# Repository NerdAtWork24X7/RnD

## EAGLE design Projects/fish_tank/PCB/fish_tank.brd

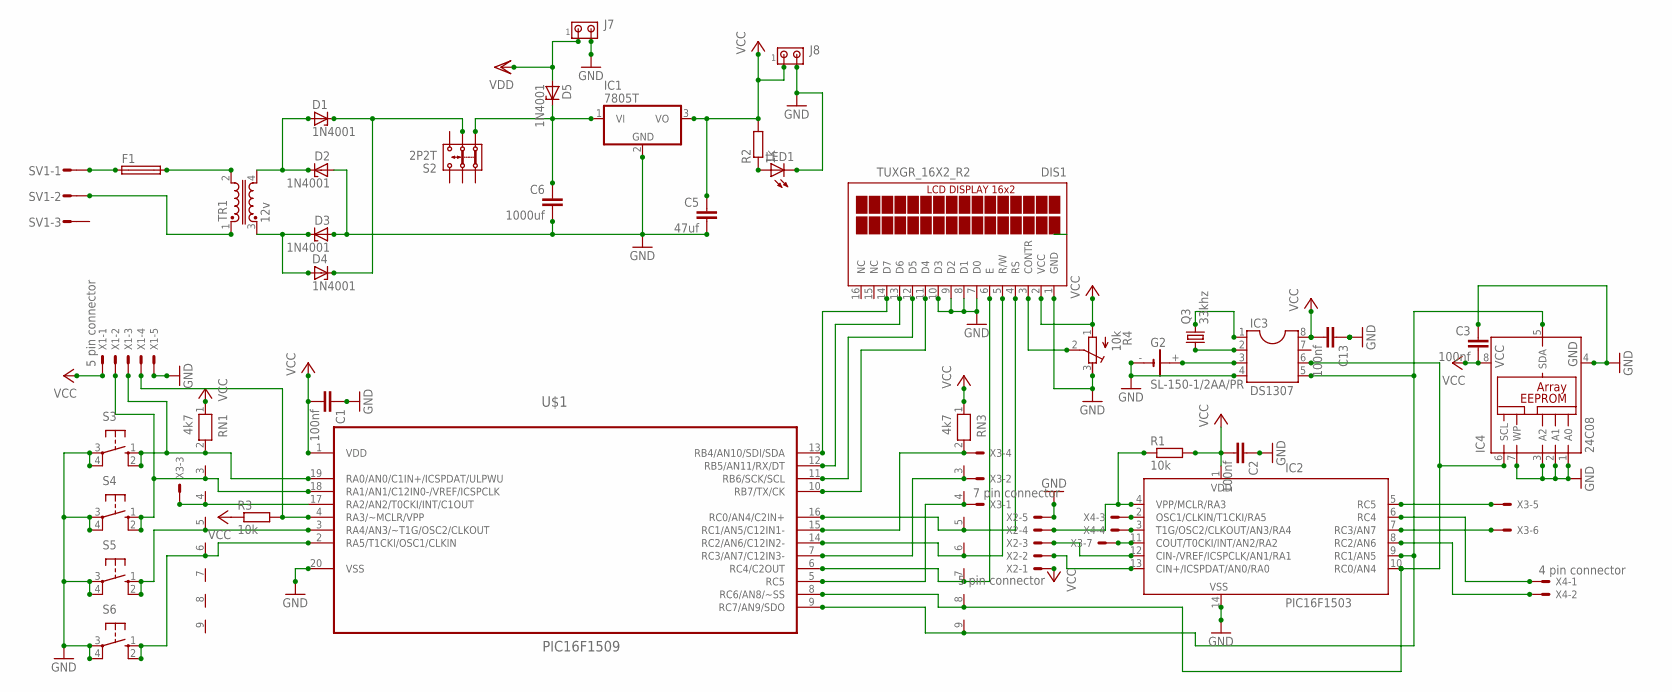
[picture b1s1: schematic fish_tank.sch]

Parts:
C1, C2: 100nf; C2.5-4
C3, C13: 100nf; C5B2.5
C5: 47uf; C5B2.5
C6: 1000uf; C5B2.5
D1, D2, D3, D4, D5: 1N4001; DO35Z10
DIS1: TUXGR_16X2_R2
F1: SH25
G2: SL-150-1/2AA/PR
IC1: 7805T; TO220H
IC2: PIC16F1503; DIL14
IC3: DS1307; DIL08
IC4: 24C08; DIL8
J7, J8: MTA02-100; 10X02MTA
LED1: LED3MM
Q3: 33khz; TC26H
R1, R3: 10k; 0207/7
R2: 1k; 0204/5
R4: 10k; RTRIM64W
RN1, RN3: 4k7; RN-9
S2: 2P2T
S3, S4, S5, S6: 10-XX; B3F-10XX
SV1: MT6-3Y
TR1: 12v; U15
U$1: PIC16F1509; DIP254P762X533-20
X1, X2: 5 pin connector; 22-23-2051
X3: 7 pin connector; 22-23-2071
X4: 4 pin connector; 22-23-2041

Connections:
GND: C1.1, C2.1, C3.1, C5.2, C6.2, C13.1, D2.A, D3.A, DIS1.1 (GND), DIS1.7 (D0), DIS1.8 (D1), DIS1.9 (D2), DIS1.10 (D3), G2.-, IC1.2 (GND), IC2.14 (VSS), IC3.4, IC4.1 (A0), IC4.2 (A1), IC4.3 (A2), IC4.4 (GND), IC4.7 (WP), J7.2, J8.2, LED1.K (C), R4.3 (E), S3.3, S3.4 (P1), S4.3, S4.4 (P1), S5.3, S5.4 (P1), S6.3, S6.4 (P1), U$1.20 (VSS), X1.5, X2.5
unnamed: D3.C, D4.A, TR1.3
unnamed: D1.A, D2.C, TR1.4
unnamed: RN1.5, S5.1 (S), S5.2 (S1), U$1.3 (RA4/AN3/~T1G/OSC2/CLKOUT)
unnamed: DIS1.3 (CONTR), R4.2 (S)
unnamed: RN1.6, S6.1 (S), S6.2 (S1), U$1.2 (RA5/T1CKI/OSC1/CLKIN)
unnamed: C6.1, D5.C, IC1.1 (VI), S2.1.2
unnamed: RN1.2, S3.1 (S), S3.2 (S1), U$1.19 (RA0/AN0/C1IN+/ICSPDAT/ULPWU), X1.3
unnamed: RN1.3, S4.1 (S), S4.2 (S1), U$1.18 (RA1/AN1/C12IN0-/VREF/ICSPCLK), X1.2
unnamed: IC2.13 (CIN+/ICSPDAT/AN0/RA0), X2.2
unnamed: IC2.6 (RC4), X4.1
unnamed: IC2.4 (VPP/MCLR/RA3), R1.1, X2.4
unnamed: DIS1.6 (E), RN3.7, U$1.6 (RC4/C2OUT)
unnamed: IC2.5 (RC5), X3.5
unnamed: IC2.7 (RC3/AN7), X3.6
unnamed: DIS1.4 (RS), RN3.5, U$1.16 (RC0/AN4/C2IN+)
unnamed: DIS1.5 (R/W), RN3.6, U$1.14 (RC2/AN6/C12IN2-)
unnamed: IC2.10 (RC0/AN4), IC3.6, IC4.6 (SCL), RN3.8, U$1.8 (RC6/AN8/~SS)
unnamed: IC2.11 (COUT/T0CKI/INT/AN2/RA2), X3.7
unnamed: IC2.12 (CIN-/VREF/ICSPCLK/AN1/RA1), X2.3
unnamed: IC2.9 (RC1/AN5), IC3.5, IC4.5 (SDA), RN3.9, U$1.9 (RC7/AN9/SDO)
unnamed: RN1.4, U$1.17 (RA2/AN2/T0CKI/INT/C1OUT), X3.3
unnamed: RN3.2, U$1.15 (RC1/AN5/C12IN1-), X3.4
unnamed: RN3.3, U$1.7 (RC3/AN7/C12IN3-), X3.2
unnamed: RN3.4, U$1.5 (RC5), X3.1
unnamed: DIS1.14 (D7), U$1.13 (RB4/AN10/SDI/SDA)
unnamed: DIS1.13 (D6), U$1.12 (RB5/AN11/RX/DT)
unnamed: DIS1.12 (D5), U$1.11 (RB6/SCK/SCL)
unnamed: DIS1.11 (D4), U$1.10 (RB7/TX/CK)
unnamed: R3.2, U$1.4 (RA3/~MCLR/VPP), X1.4
unnamed: IC2.8 (RC2/AN6), X4.2
unnamed: IC2.2 (OSC1/CLKIN/T1CKI/RA5), X4.3
unnamed: IC2.3 (T1G/OSC2/CLKOUT/AN3/RA4), X4.4
unnamed: SV1.2, TR1.1
unnamed: F1.1, SV1.1
unnamed: F1.2, TR1.2
unnamed: G2.+, IC3.3
unnamed: IC3.2, Q3.1
unnamed: D1.C, D4.C, S2.2.2
unnamed: LED1.A, R2.1
unnamed: IC3.1, Q3.2
VCC: C1.2, C2.2, C3.2, C5.1, C13.2, DIS1.2 (VCC), IC1.3 (VO), IC2.1 (VDD), IC3.8, IC4.8 (VCC), J8.1, R1.2, R2.2, R3.1, R4.1 (A), RN1.1, RN3.1, U$1.1 (VDD), X1.1, X2.1
VDD: D5.A, J7.1

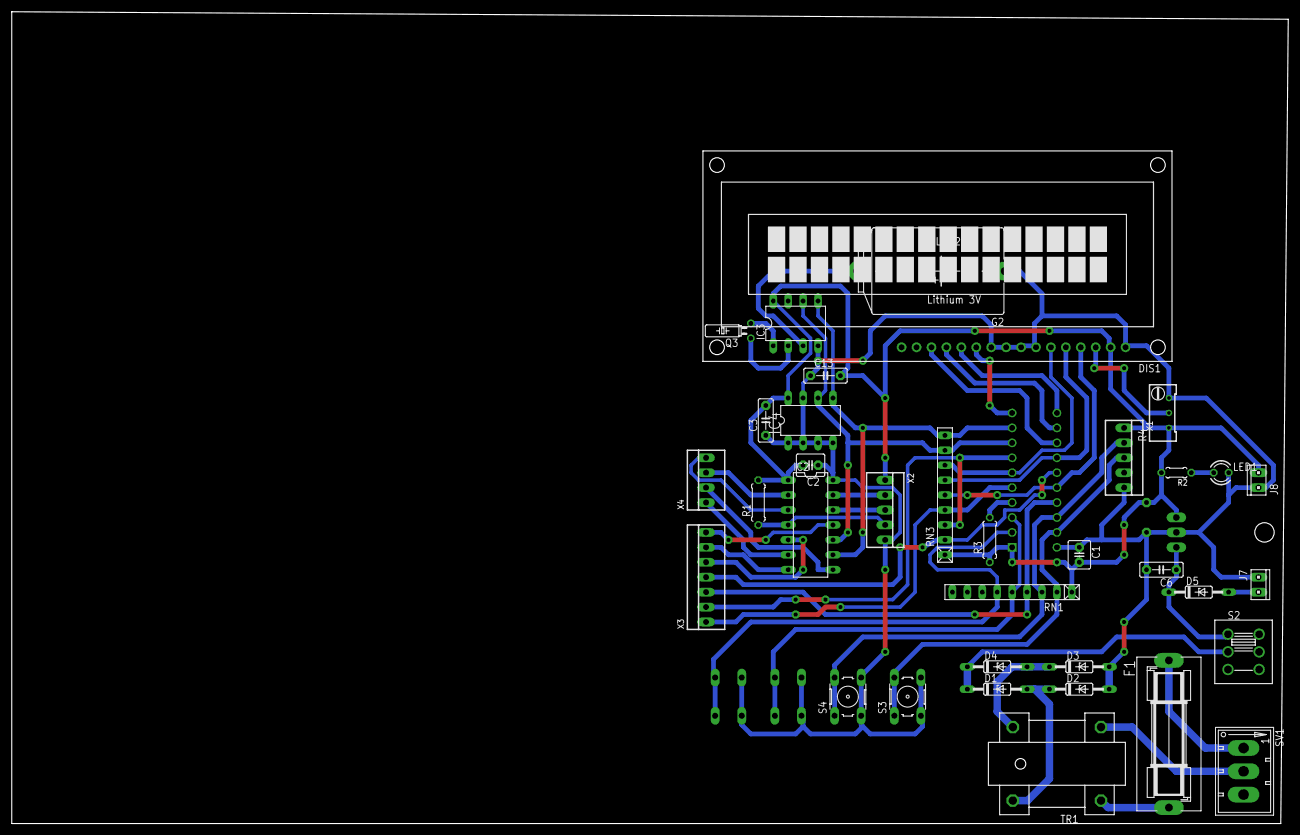
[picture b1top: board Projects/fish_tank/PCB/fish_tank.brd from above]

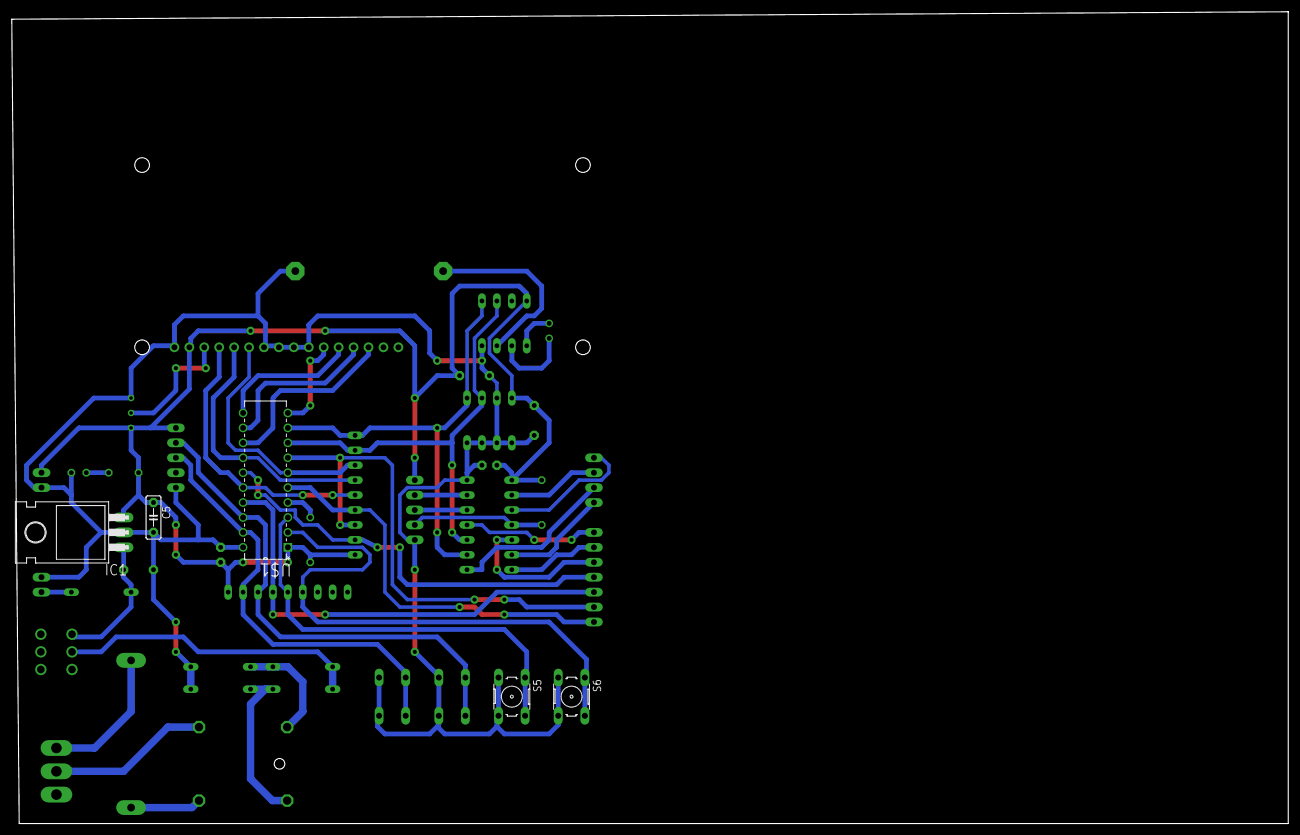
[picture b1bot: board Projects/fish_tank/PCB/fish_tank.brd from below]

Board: 2 copper layers, 217.2 x 138.1 mm, 40 parts (5 on the bottom side), 43 nets.

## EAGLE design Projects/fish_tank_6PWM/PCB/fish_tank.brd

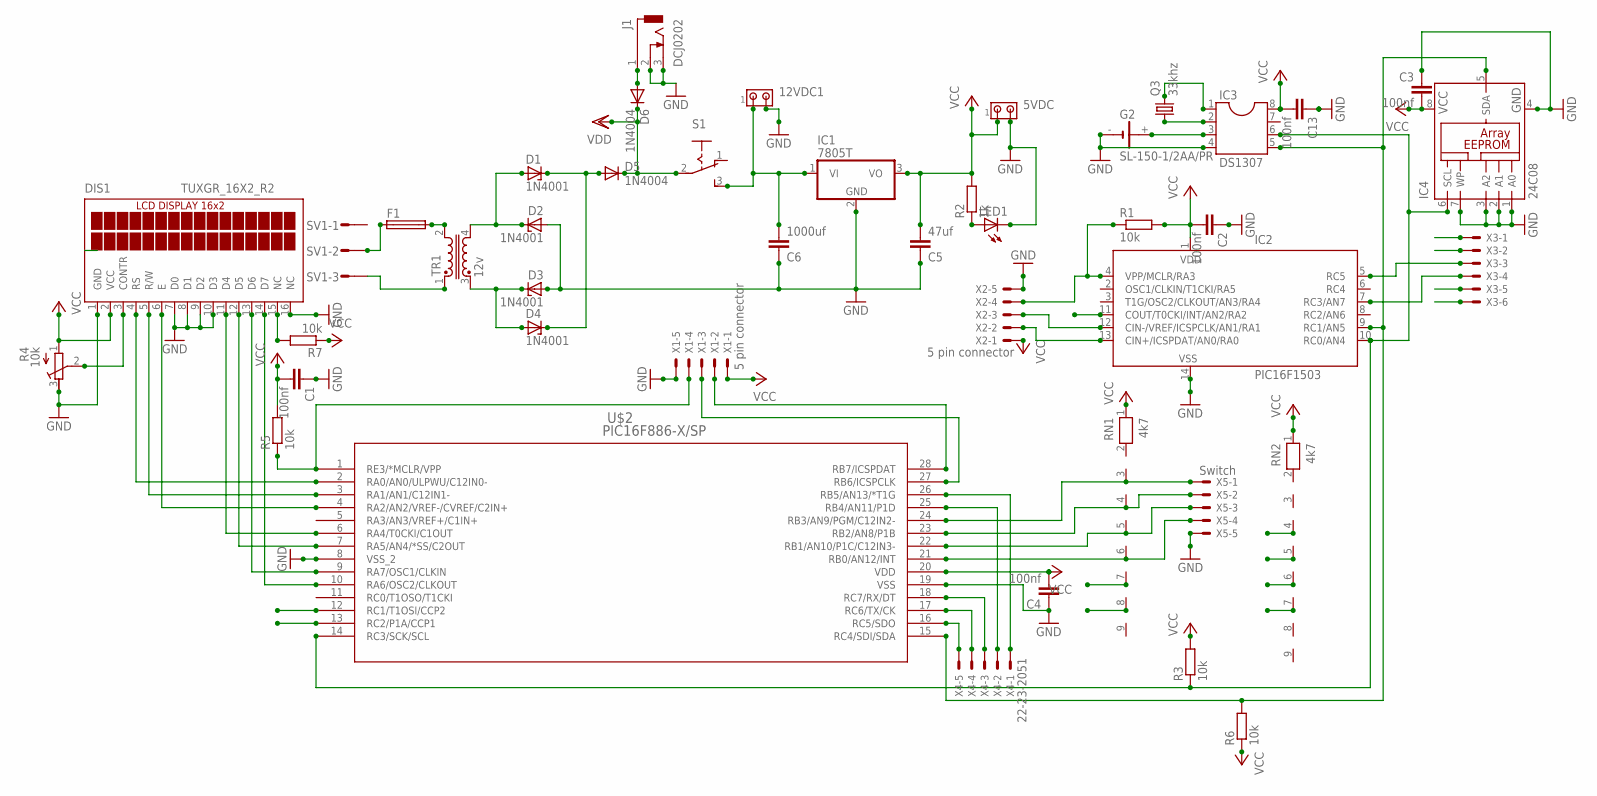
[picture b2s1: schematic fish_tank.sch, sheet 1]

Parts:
5VDC, 12VDC1: MTA02-100; 10X02MTA
C1, C2, C4: 100nf; C2.5-4
C3, C13: 100nf; C5B2.5
C5: 47uf; C5B2.5
C6: 1000uf; C5B2.5
D1, D2, D3, D4: 1N4001; DO35Z10
D5, D6: 1N4004; DO41-10
DIS1: TUXGR_16X2_R2
F1: SH25
G2: SL-150-1/2AA/PR
IC1: 7805T; TO220H
IC2: PIC16F1503; DIL14
IC3: DS1307; DIL08
IC4: 24C08; DIL8
J1: DCJ0202
LED1: LED3MM
Q3: 33khz; TC26H
R1, R3, R5, R6, R7: 10k; 0207/7
R2: 1k; 0204/5
R4: 10k; RTRIM64W
RN1, RN2: 4k7; RN-9
S1: 255SB
SV1: MT6-3Y
TR1: 12v; U15
U$2: PIC16F886-X/SP; SPDIP28_300MC
X1, X2: 5 pin connector; 22-23-2051
X3: 22-23-2061
X4: 22-23-2051
X5: Switch; 22-23-2051

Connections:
GND: 5VDC.2, 12VDC1.2, C1.1, C2.1, C3.1, C4.1, C5.1, C6.1, C13.1, D2.A, D3.A, DIS1.1 (GND), DIS1.7 (D0), DIS1.8 (D1), DIS1.9 (D2), DIS1.10 (D3), DIS1.16 (NC), G2.-, IC1.2 (GND), IC2.14 (VSS), IC3.4, IC4.1 (A0), IC4.2 (A1), IC4.3 (A2), IC4.4 (GND), IC4.7 (WP), J1.2, J1.3, LED1.K (C), R4.3 (E), U$2.8 (VSS_2), U$2.19 (VSS), X1.5, X2.5, X5.5
unnamed: D3.C, D4.A, TR1.3
unnamed: D1.A, D2.C, TR1.4
unnamed: RN1.5, U$2.22 (RB1/AN10/P1C/C12IN3-), X5.3
unnamed: DIS1.3 (CONTR), R4.2 (S)
unnamed: RN1.6, U$2.21 (RB0/AN12/INT), X5.4
unnamed: IC2.10 (RC0/AN4), IC3.6, IC4.6 (SCL), R3.1, U$2.14 (RC3/SCK/SCL)
unnamed: RN1.3, U$2.24 (RB3/AN9/PGM/C12IN2-), X5.1
unnamed: DIS1.4 (RS), U$2.2 (RA0/AN0/ULPWU/C12IN0-)
unnamed: IC2.13 (CIN+/ICSPDAT/AN0/RA0), X2.2
unnamed: DIS1.5 (R/W), U$2.3 (RA1/AN1/C12IN1-)
unnamed: IC2.4 (VPP/MCLR/RA3), R1.1, X2.4
unnamed: DIS1.6 (E), U$2.4 (RA2/AN2/VREF-/CVREF/C2IN+)
unnamed: IC2.9 (RC1/AN5), IC3.5, IC4.5 (SDA), R6.2, U$2.15 (RC4/SDI/SDA)
unnamed: U$2.26 (RB5/AN13/*T1G), X4.1
unnamed: F1.1, SV1.2
unnamed: U$2.25 (RB4/AN11/P1D), X4.2
unnamed: U$2.16 (RC5/SDO), X4.5
unnamed: U$2.17 (RC6/TX/CK), X4.4
unnamed: IC2.12 (CIN-/VREF/ICSPCLK/AN1/RA1), X2.3
unnamed: U$2.18 (RC7/RX/DT), X4.3
unnamed: RN1.4, U$2.23 (RB2/AN8/P1B), X5.2
unnamed: D6.A, J1.1
unnamed: 12VDC1.1, C6.2, IC1.1 (VI), S1.3 (S)
unnamed: IC2.7 (RC3/AN7), X3.4
unnamed: DIS1.14 (D7), U$2.10 (RA6/OSC2/CLKOUT)
unnamed: DIS1.13 (D6), U$2.9 (RA7/OSC1/CLKIN)
unnamed: DIS1.12 (D5), U$2.7 (RA5/AN4/*SS/C2OUT)
unnamed: DIS1.11 (D4), U$2.6 (RA4/T0CKI/C1OUT)
unnamed: U$2.27 (RB6/ICSPCLK), X1.3
unnamed: DIS1.15 (NC), R7.2
unnamed: U$2.28 (RB7/ICSPDAT), X1.2
unnamed: R5.1, U$2.1 (RE3/*MCLR/VPP), X1.4
unnamed: SV1.3, TR1.1
unnamed: F1.2, TR1.2
unnamed: G2.+, IC3.3
unnamed: IC3.2, Q3.1
unnamed: D1.C, D4.C, D5.A
unnamed: LED1.A, R2.1
unnamed: IC3.1, Q3.2
PWM1: RN1.7, U$2.13 (RC2/P1A/CCP1), X3.1
PWM2: RN1.8, U$2.12 (RC1/T1OSI/CCP2), X3.2
PWM3: IC2.5 (RC5), RN2.4, X3.3
PWM4: RN2.5
PWM5: IC2.11 (COUT/T0CKI/INT/AN2/RA2), RN2.6, X3.5
PWM6: RN2.7, X3.6
VCC: 5VDC.1, C1.2, C2.2, C3.2, C4.2, C5.2, C13.2, DIS1.2 (VCC), IC1.3 (VO), IC2.1 (VDD), IC3.8, IC4.8 (VCC), R1.2, R2.2, R3.2, R4.1 (A), R5.2, R6.1, R7.1, RN1.1, RN2.1, U$2.20 (VDD), X1.1, X2.1
VDD: D5.C, D6.C, S1.2

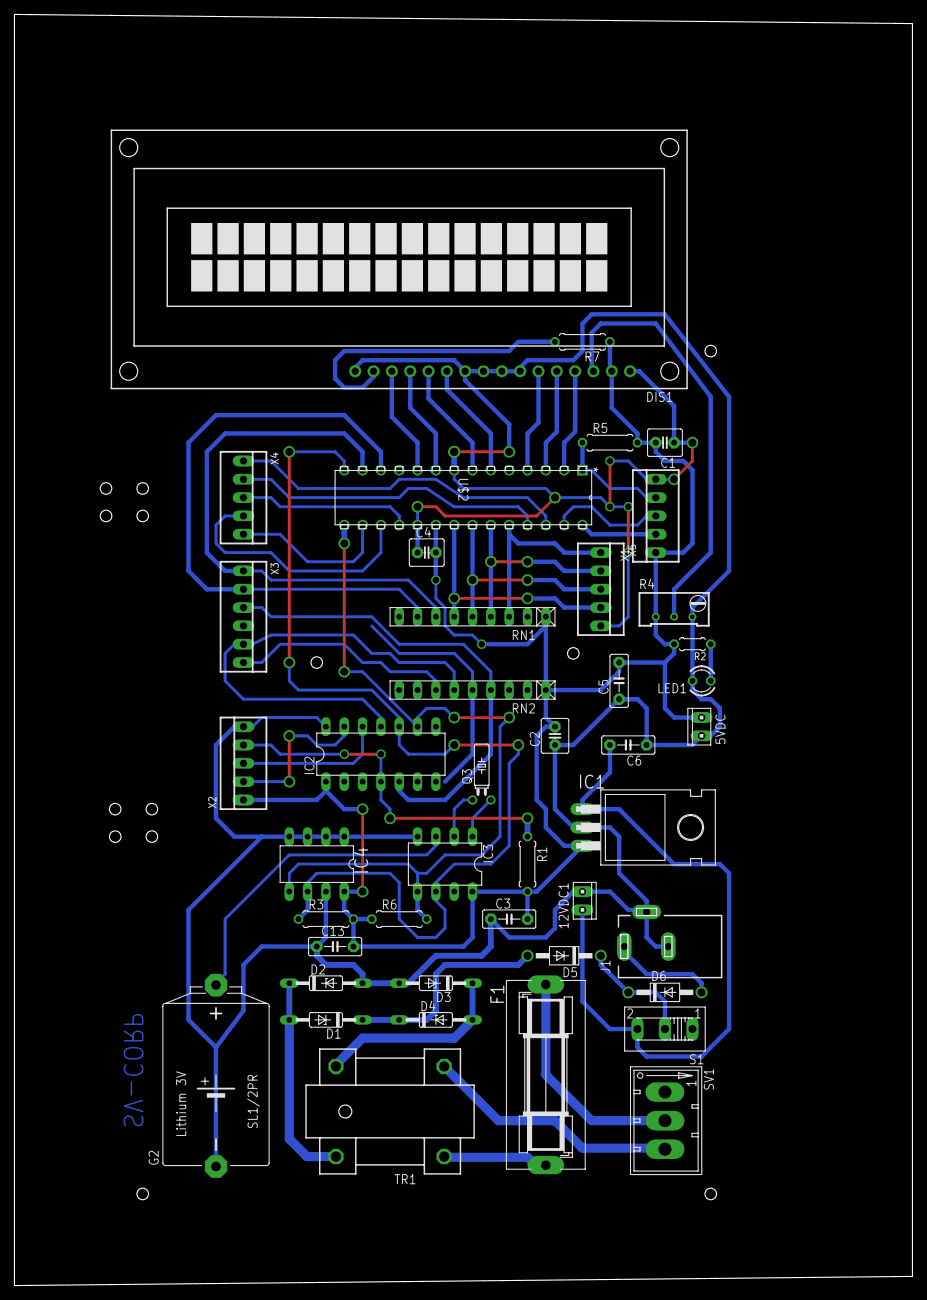
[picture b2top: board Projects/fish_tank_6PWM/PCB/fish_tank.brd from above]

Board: 2 copper layers, 124.5 x 176.2 mm, 43 parts (0 on the bottom side), 47 nets.

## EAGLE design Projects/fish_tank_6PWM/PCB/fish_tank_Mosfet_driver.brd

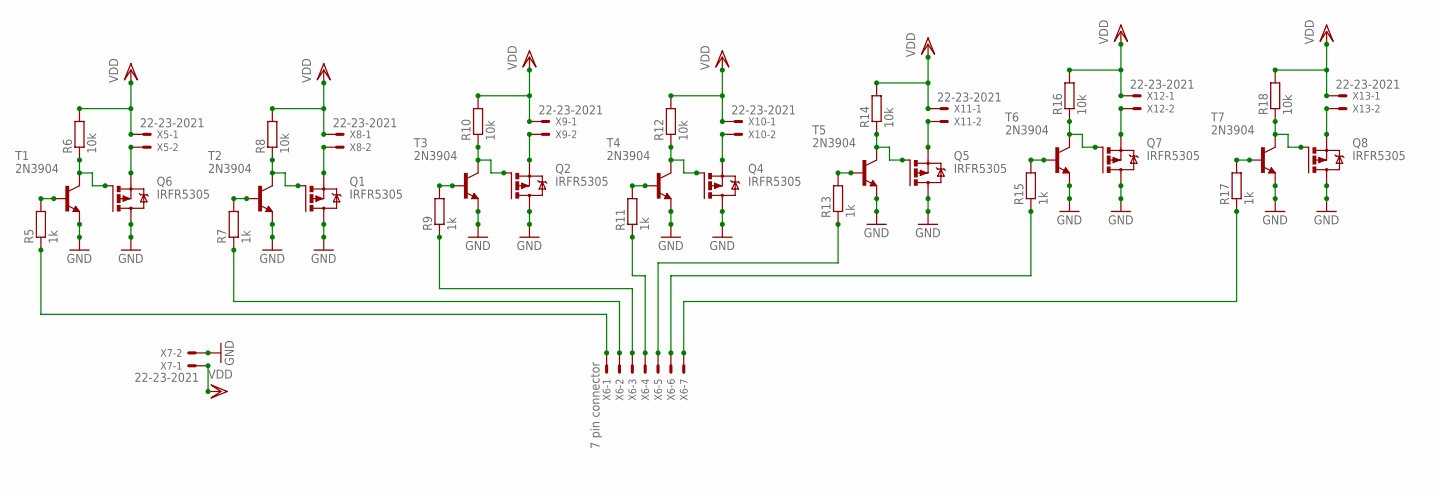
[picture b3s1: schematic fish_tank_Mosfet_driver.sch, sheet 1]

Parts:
Q1, Q2, Q4, Q5, Q6, Q7, Q8: IRFR5305; D-PAK_TO252AA
R5, R7, R9, R11, R13, R15, R17: 1k; 0207/7
R6, R8, R10, R12, R14, R16, R18: 10k; 0207/7
T1, T2, T3, T4, T5, T6, T7: 2N3904; TO92
X5, X7, X8, X9, X10, X11, X12, X13: 22-23-2021
X6: 7 pin connector; 22-23-2071

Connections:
GND: Q1.4 (D), Q2.4 (D), Q4.4 (D), Q5.4 (D), Q6.4 (D), Q7.4 (D), Q8.4 (D), T1.3 (E), T2.3 (E), T3.3 (E), T4.3 (E), T5.3 (E), T6.3 (E), T7.3 (E), X7.2
unnamed: Q6.1 (G), R6.1, T1.1 (C)
unnamed: R5.2, T1.2 (B)
unnamed: Q6.3 (S), X5.2
unnamed: R5.1, X6.1
unnamed: Q1.1 (G), R8.1, T2.1 (C)
unnamed: R7.2, T2.2 (B)
unnamed: Q1.3 (S), X8.2
unnamed: R7.1, X6.2
unnamed: Q2.1 (G), R10.1, T3.1 (C)
unnamed: R9.2, T3.2 (B)
unnamed: Q2.3 (S), X9.2
unnamed: R9.1, X6.3
unnamed: Q4.1 (G), R12.1, T4.1 (C)
unnamed: R11.2, T4.2 (B)
unnamed: Q4.3 (S), X10.2
unnamed: R11.1, X6.4
unnamed: Q5.1 (G), R14.1, T5.1 (C)
unnamed: R13.2, T5.2 (B)
unnamed: Q5.3 (S), X11.2
unnamed: R13.1, X6.5
unnamed: Q7.1 (G), R16.1, T6.1 (C)
unnamed: R15.2, T6.2 (B)
unnamed: Q7.3 (S), X12.2
unnamed: R15.1, X6.6
unnamed: Q8.1 (G), R18.1, T7.1 (C)
unnamed: R17.2, T7.2 (B)
unnamed: Q8.3 (S), X13.2
unnamed: R17.1, X6.7
VDD: R6.2, R8.2, R10.2, R12.2, R14.2, R16.2, R18.2, X5.1, X7.1, X8.1, X9.1, X10.1, X11.1, X12.1, X13.1

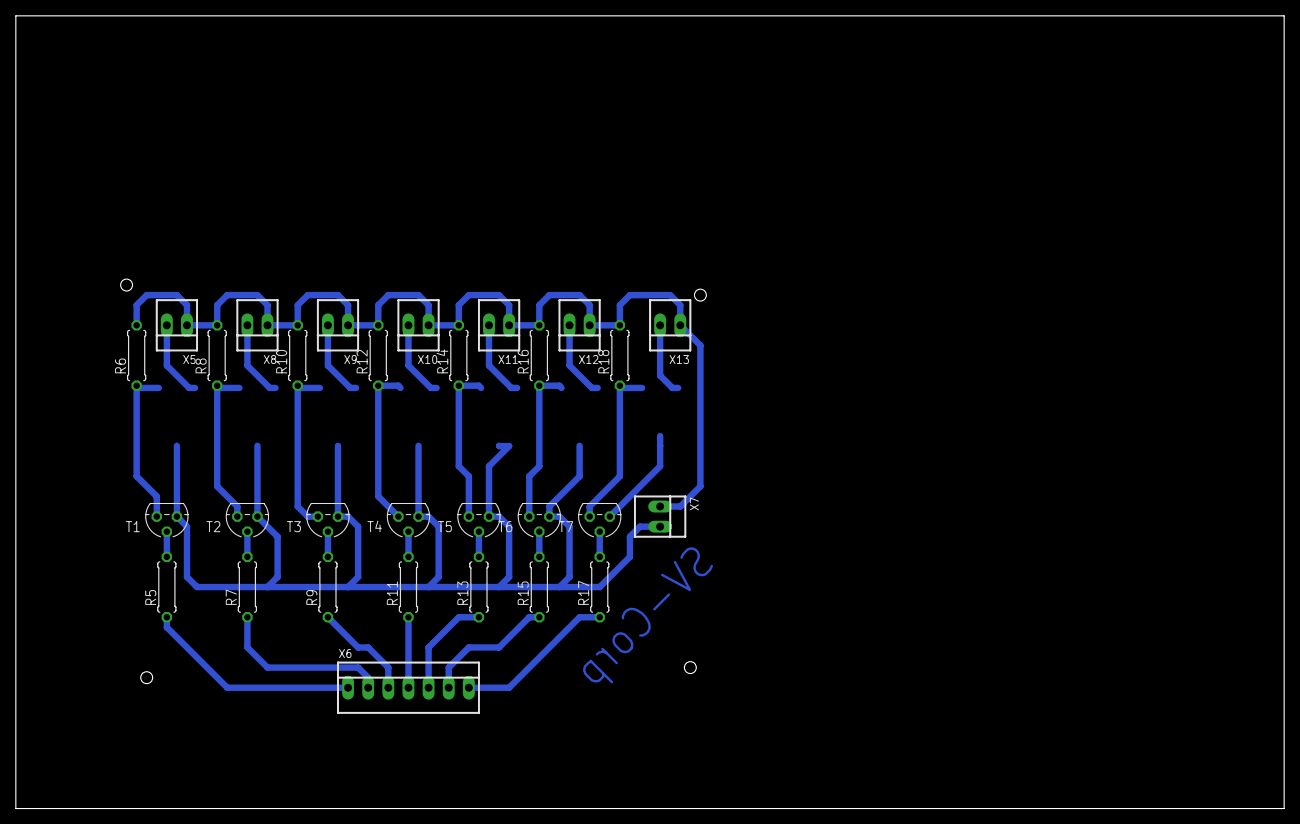
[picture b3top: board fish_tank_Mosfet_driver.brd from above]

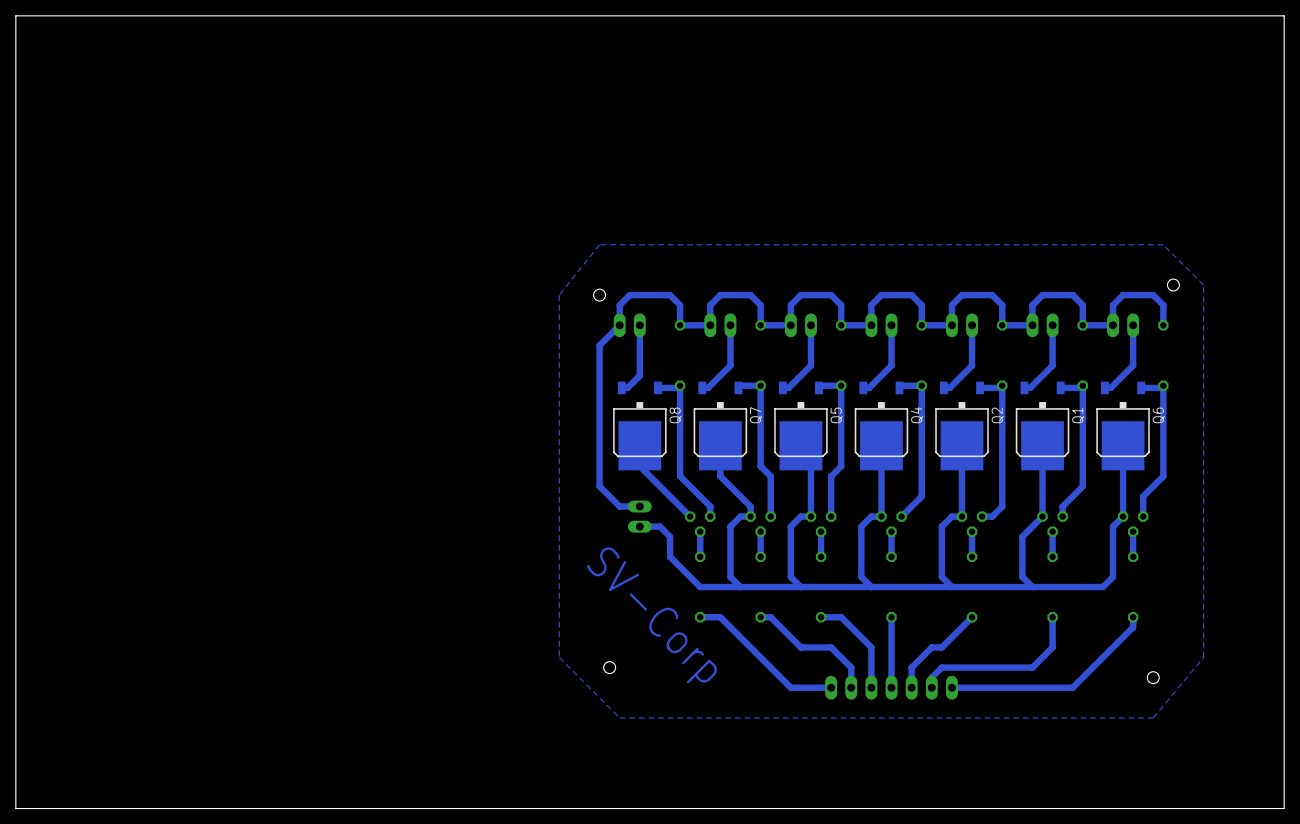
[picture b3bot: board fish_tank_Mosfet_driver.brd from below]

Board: 2 copper layers, 160.0 x 100.0 mm, 37 parts (7 on the bottom side), 30 nets.

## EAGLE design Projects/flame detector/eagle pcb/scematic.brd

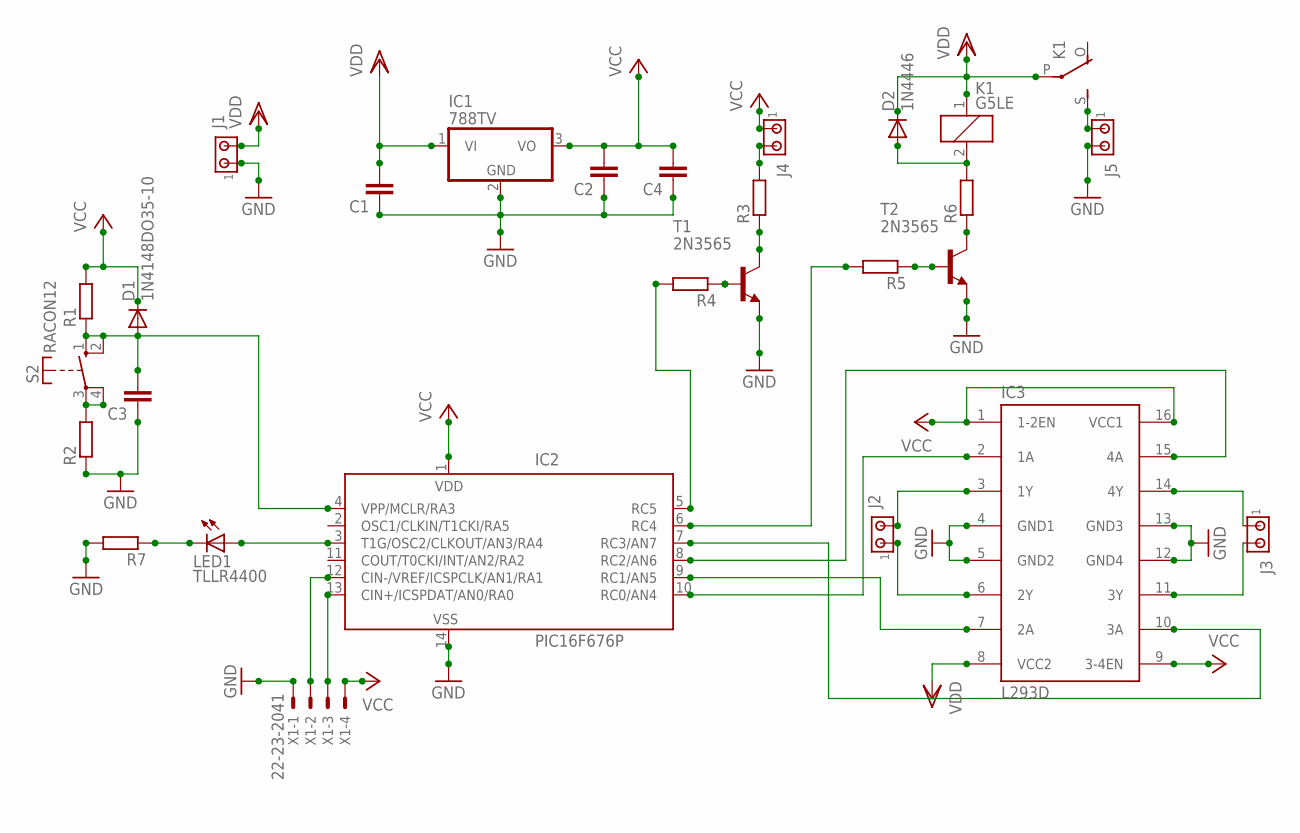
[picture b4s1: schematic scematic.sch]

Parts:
C1, C2, C3, C4: C7.5/3; C7.5B3
D1: 1N4148DO35-10; DO35-10
D2: 1N4446; DO35-10
IC1: 788TV; TO220V
IC2: PIC16F676P; DIL14
IC3: L293D; DIL16
J1, J2, J3, J4, J5: MTA02-156; 1X2MTA
K1: G5LE
LED1: TLLR4400; LED3MM
R1, R2, R3, R4, R5, R6, R7: R-EU_0207/10; 0207/10
S2: RACON12
T1, T2: 2N3565; TO92
X1: 22-23-2041

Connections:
GND: C1.1, C2.1, C3.1, C4.1, IC1.2 (GND), IC2.14 (VSS), IC3.4 (GND1), IC3.5 (GND2), IC3.12 (GND4), IC3.13 (GND3), J1.1, J5.2, R2.1, R7.2, T1.3 (E), T2.3 (E), X1.1
unnamed: C3.2, D1.A, IC2.4 (VPP/MCLR/RA3), R1.1, S2.1 (S), S2.2 (S)
unnamed: IC2.10 (RC0/AN4), IC3.2 (1A)
unnamed: IC2.9 (RC1/AN5), IC3.7 (2A)
unnamed: R2.2, S2.3, S2.4
unnamed: IC3.3 (1Y), J2.2
unnamed: IC3.6 (2Y), J2.1
unnamed: IC3.14 (4Y), J3.1
unnamed: IC3.11 (3Y), J3.2
unnamed: IC2.8 (RC2/AN6), IC3.15 (4A)
unnamed: IC2.7 (RC3/AN7), IC3.10 (3A)
unnamed: IC2.5 (RC5), R4.2
unnamed: R4.1, T1.2 (B)
unnamed: R3.1, T1.1 (C)
unnamed: J4.2, R3.2
unnamed: IC2.6 (RC4), R5.2
unnamed: R5.1, T2.2 (B)
unnamed: R6.1, T2.1 (C)
unnamed: D2.A, K1.2, R6.2
unnamed: J5.1, K1.S
unnamed: IC2.13 (CIN+/ICSPDAT/AN0/RA0), X1.3
unnamed: IC2.12 (CIN-/VREF/ICSPCLK/AN1/RA1), X1.2
unnamed: IC2.3 (T1G/OSC2/CLKOUT/AN3/RA4), LED1.A
unnamed: LED1.K (C), R7.1
VCC: C2.2, C4.2, D1.C, IC1.3 (VO), IC2.1 (VDD), IC3.1 (1-2EN), IC3.9 (3-4EN), IC3.16 (VCC1), J4.1, R1.2, X1.4
VDD: C1.2, D2.C, IC1.1 (VI), IC3.8 (VCC2), J1.2, K1.1, K1.P

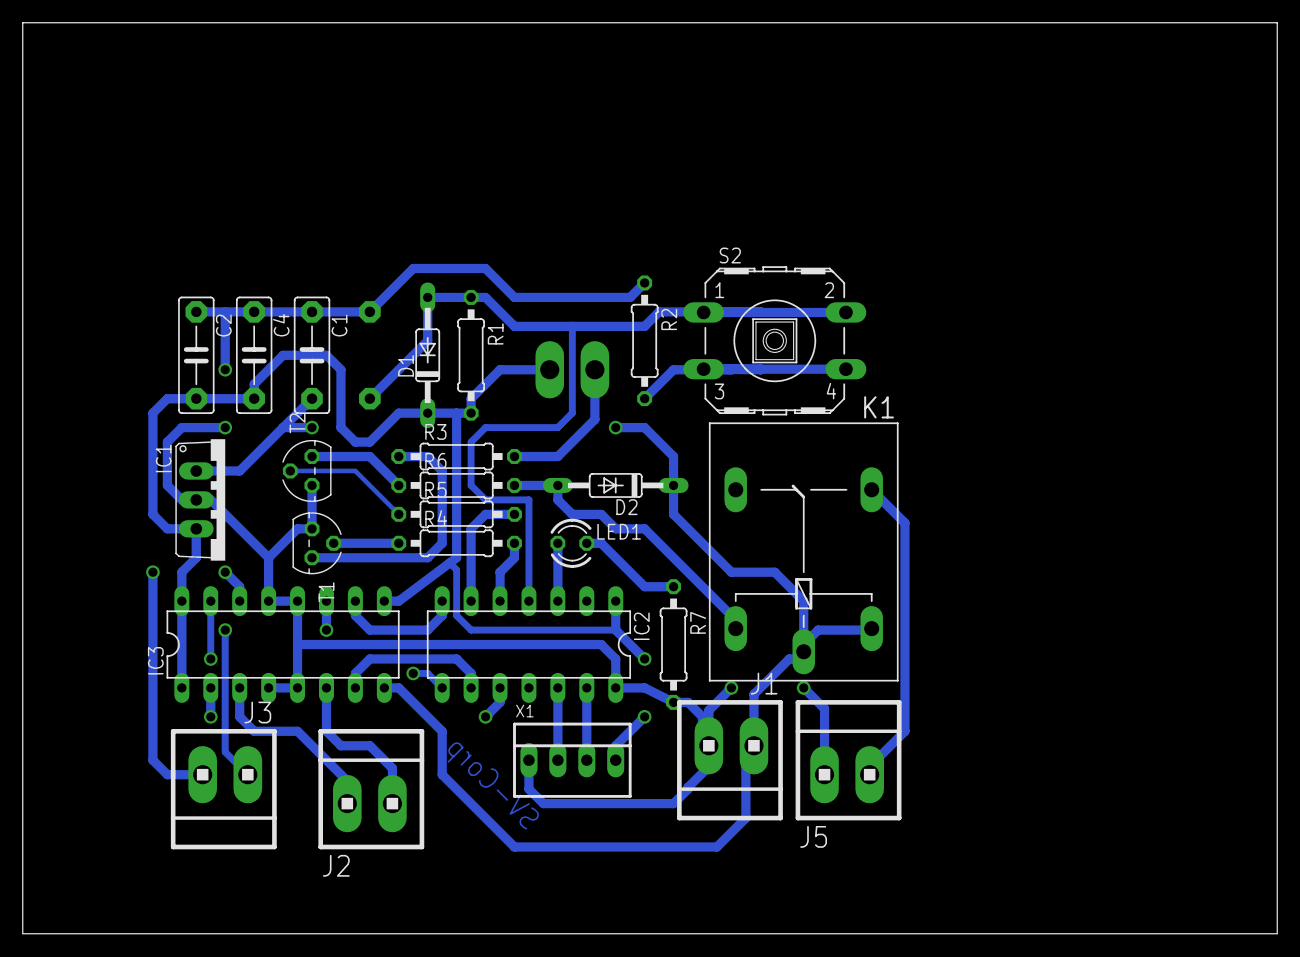
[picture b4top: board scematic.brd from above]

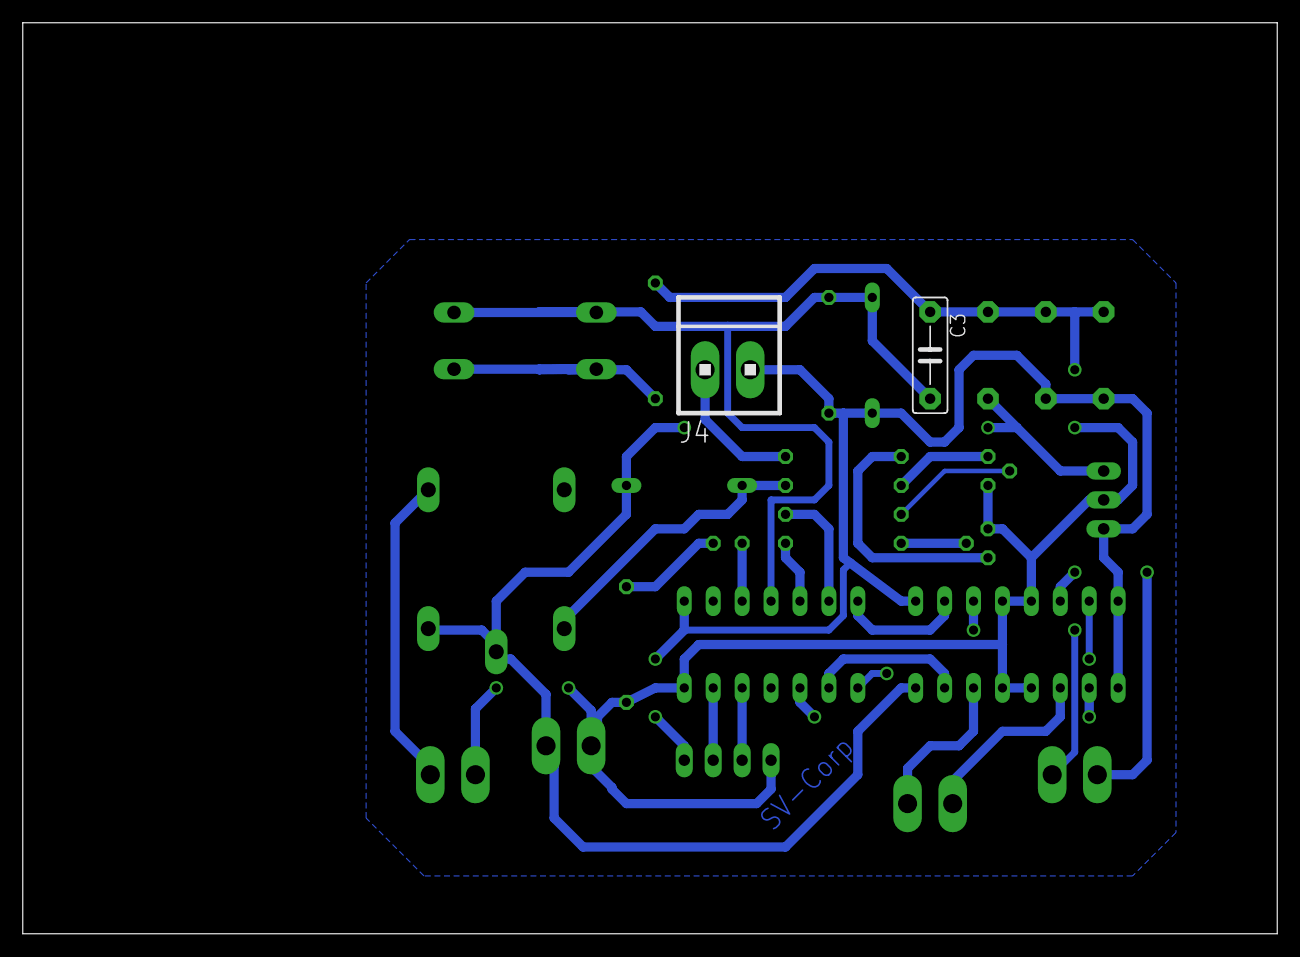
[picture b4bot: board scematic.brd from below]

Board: 2 copper layers, 110.2 x 80.0 mm, 27 parts (2 on the bottom side), 26 nets.

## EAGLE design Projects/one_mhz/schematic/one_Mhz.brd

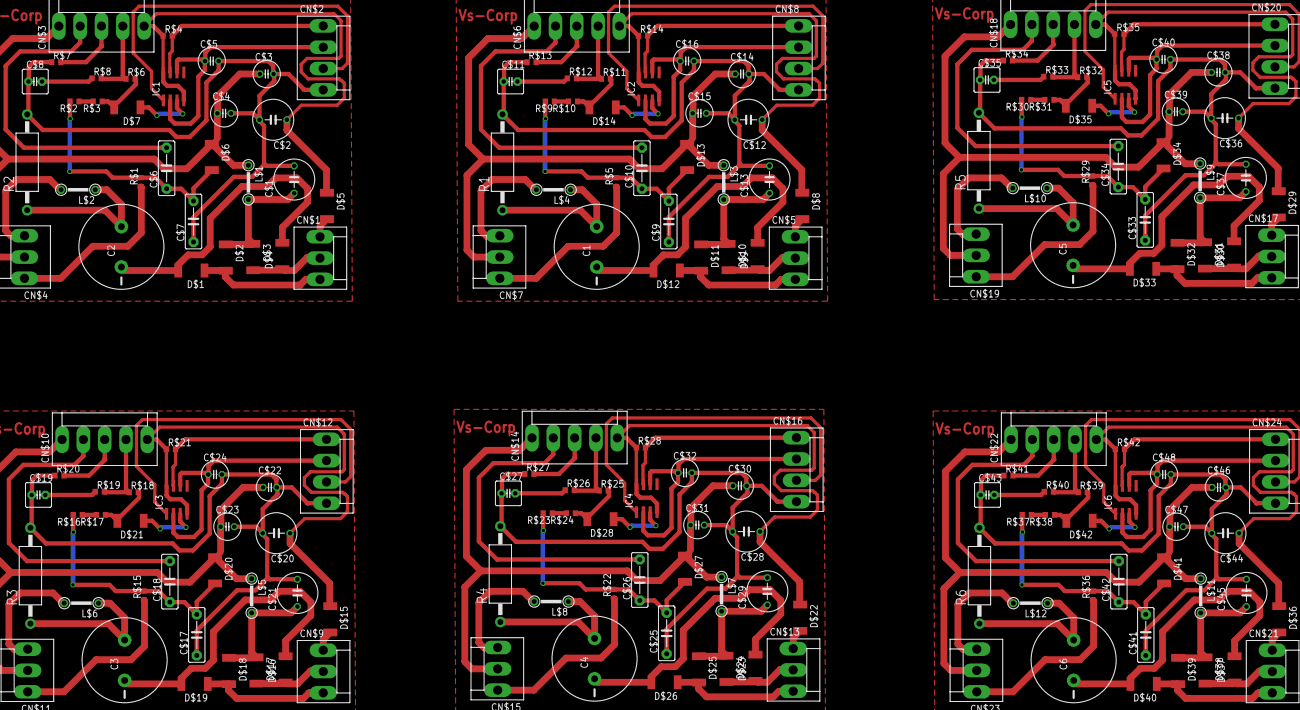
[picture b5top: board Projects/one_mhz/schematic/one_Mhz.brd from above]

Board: 2 copper layers, 186 parts (0 on the bottom side), 132 nets.

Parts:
C1, C2, C3, C4, C5, C6: SANYO-OSCON_H
C$1, C$2, C$12, C$13, C$20, C$21, C$28, C$29, C$36, C$37, C$44, C$45: C050-075X075
C$3, C$4, C$5, C$14, C$15, C$16, C$22, C$23, C$24, C$30, C$31, C$32, C$38, C$39, C$40, C$46, C$47, C$48: C025-050X050
C$6, C$7, C$9, C$10, C$17, C$18, C$25, C$26, C$33, C$34, C$41, C$42: C7.5B3
C$8, C$11, C$19, C$27, C$35, C$43: C2.5-5
CN$1, CN$4, CN$5, CN$7, CN$9, CN$11, CN$13, CN$15, CN$17, CN$19, CN$21, CN$23: KK-156-3
CN$2, CN$8, CN$12, CN$16, CN$20, CN$24: KK-156-4
CN$3, CN$6, CN$10, CN$14, CN$18, CN$22: KK-156-5
D$1, D$2, D$3, D$4, D$5, D$6, D$7, D$8, D$9, D$10, D$11, D$12, D$13, D$14, D$15, D$16, D$17, D$18, D$19, D$20, D$21, D$22, D$23, D$24, D$25, D$26, D$27, D$28, D$29, D$30, D$31, D$32, D$33, D$34, D$35, D$36, D$37, D$38, D$39, D$40, D$41, D$42: SOD87
IC1, IC2, IC3, IC4, IC5, IC6: UA555D; SO08
L$1, L$2, L$3, L$4, L$5, L$6, L$7, L$8, L$9, L$10, L$11, L$12: BL03RN2
R1, R2, R3, R4, R5, R6: AC01
R$1, R$5, R$15, R$22, R$29, R$36: R0603
R$2, R$3, R$9, R$10, R$16, R$17, R$23, R$24, R$30, R$31, R$37, R$38: 1.5K; R0603
R$4, R$6, R$7, R$8, R$11, R$12, R$13, R$14, R$18, R$19, R$20, R$21, R$25, R$26, R$27, R$28, R$32, R$33, R$34, R$35, R$39, R$40, R$41, R$42: 100; R0603

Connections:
unnamed: C$3.1, C$4.1, CN$3.1, CN$4.2, D$6.1, L$1.1
unnamed: CN$1.2, D$3.2, D$4.1
unnamed: CN$5.2, D$9.1, D$10.2
unnamed: CN$5.3, D$11.2, D$12.1
unnamed: C1.-, D$9.2, D$12.2
unnamed: CN$1.3, D$1.1, D$2.2
unnamed: C2.-, D$1.2, D$4.2
unnamed: CN$5.1, D$8.2
unnamed: CN$1.1, D$5.2
unnamed: R$9.1, R$10.2
unnamed: D$14.2, R$10.1, R$11.2
unnamed: C$1.2, C$2.2, C$3.2, C$4.2, C$5.2, C$7.1, C$8.1, CN$2.4, R2.2, R$7.1
unnamed: R$2.1, R$3.2
unnamed: D$7.2, R$3.1, R$6.2
unnamed: D$7.1, IC1.3
unnamed: CN$3.4, R$6.1, R$8.2
unnamed: C$8.2, R$8.1
unnamed: D$14.1, IC2.3
unnamed: C$5.1, CN$2.2, IC1.2, IC1.6
unnamed: CN$3.3, R$7.2
unnamed: CN$4.3, L$2.2
unnamed: C2.+, L$2.1, R2.1
unnamed: CN$6.4, R$11.1, R$12.2
unnamed: C$6.2, CN$3.2
unnamed: C$11.2, R$12.1
unnamed: C$6.1, C$7.2, D$6.2, R$1.2, R$2.2
unnamed: C$1.1, D$2.1, D$3.1, L$1.2
unnamed: C$2.1, CN$3.5, D$5.1, IC1.4, IC1.8, R$4.1
unnamed: CN$6.3, R$13.2
unnamed: CN$7.3, L$4.2
unnamed: C1.+, L$4.1, R1.1
unnamed: C$10.2, CN$6.2
unnamed: CN$4.1, R$1.1
unnamed: C$9.2, C$10.1, D$13.2, R$5.2, R$9.2
unnamed: CN$2.1, IC1.7, R$4.2
unnamed: C$9.1, C$11.1, C$12.2, C$13.2, C$14.2, C$15.2, C$16.2, CN$8.4, R1.2, R$13.1
unnamed: CN$2.3, IC1.1
unnamed: C$16.1, CN$8.2, IC2.2, IC2.6
unnamed: C$13.1, D$10.1, D$11.1, L$3.2
unnamed: C$12.1, CN$6.5, D$8.1, IC2.4, IC2.8, R$14.1
unnamed: CN$8.1, IC2.7, R$14.2
unnamed: CN$8.3, IC2.1
unnamed: CN$7.1, R$5.1
unnamed: C$14.1, C$15.1, CN$6.1, CN$7.2, D$13.1, L$3.1
unnamed: CN$9.2, D$16.1, D$17.2
unnamed: CN$9.3, D$18.2, D$19.1
unnamed: C3.-, D$16.2, D$19.2
unnamed: CN$9.1, D$15.2
unnamed: R$16.1, R$17.2
unnamed: D$21.2, R$17.1, R$18.2
unnamed: D$21.1, IC3.3
unnamed: CN$10.4, R$18.1, R$19.2
unnamed: C$19.2, R$19.1
unnamed: CN$10.3, R$20.2
unnamed: CN$11.3, L$6.2
unnamed: C3.+, L$6.1, R3.1
unnamed: C$18.2, CN$10.2
unnamed: C$17.2, C$18.1, D$20.2, R$15.2, R$16.2
unnamed: C$17.1, C$19.1, C$20.2, C$21.2, C$22.2, C$23.2, C$24.2, CN$12.4, R3.2, R$20.1
unnamed: C$24.1, CN$12.2, IC3.2, IC3.6
unnamed: C$21.1, D$17.1, D$18.1, L$5.2
unnamed: C$20.1, CN$10.5, D$15.1, IC3.4, IC3.8, R$21.1
unnamed: CN$12.1, IC3.7, R$21.2
unnamed: CN$12.3, IC3.1
unnamed: CN$11.1, R$15.1
unnamed: C$22.1, C$23.1, CN$10.1, CN$11.2, D$20.1, L$5.1
unnamed: CN$13.2, D$23.1, D$24.2
unnamed: CN$13.3, D$25.2, D$26.1
unnamed: C4.-, D$23.2, D$26.2
unnamed: CN$13.1, D$22.2
unnamed: R$23.1, R$24.2
unnamed: D$28.2, R$24.1, R$25.2
unnamed: D$28.1, IC4.3
unnamed: CN$14.4, R$25.1, R$26.2
unnamed: C$27.2, R$26.1
unnamed: CN$14.3, R$27.2
unnamed: CN$15.3, L$8.2
unnamed: C4.+, L$8.1, R4.1
unnamed: C$26.2, CN$14.2
unnamed: C$25.2, C$26.1, D$27.2, R$22.2, R$23.2
unnamed: C$25.1, C$27.1, C$28.2, C$29.2, C$30.2, C$31.2, C$32.2, CN$16.4, R4.2, R$27.1
unnamed: C$32.1, CN$16.2, IC4.2, IC4.6
unnamed: C$29.1, D$24.1, D$25.1, L$7.2
unnamed: C$28.1, CN$14.5, D$22.1, IC4.4, IC4.8, R$28.1
unnamed: CN$16.1, IC4.7, R$28.2
unnamed: CN$16.3, IC4.1
unnamed: CN$15.1, R$22.1
unnamed: C$30.1, C$31.1, CN$14.1, CN$15.2, D$27.1, L$7.1
unnamed: CN$17.2, D$30.1, D$31.2
unnamed: CN$17.3, D$32.2, D$33.1
unnamed: C5.-, D$30.2, D$33.2
unnamed: CN$17.1, D$29.2
unnamed: R$30.1, R$31.2
unnamed: D$35.2, R$31.1, R$32.2
unnamed: D$35.1, IC5.3
unnamed: CN$18.4, R$32.1, R$33.2
unnamed: C$35.2, R$33.1
unnamed: CN$18.3, R$34.2
unnamed: CN$19.3, L$10.2
unnamed: C5.+, L$10.1, R5.1
unnamed: C$34.2, CN$18.2
unnamed: C$33.2, C$34.1, D$34.2, R$29.2, R$30.2
unnamed: C$33.1, C$35.1, C$36.2, C$37.2, C$38.2, C$39.2, C$40.2, CN$20.4, R5.2, R$34.1
unnamed: C$40.1, CN$20.2, IC5.2, IC5.6
unnamed: C$37.1, D$31.1, D$32.1, L$9.2
unnamed: C$36.1, CN$18.5, D$29.1, IC5.4, IC5.8, R$35.1
unnamed: CN$20.1, IC5.7, R$35.2
unnamed: CN$20.3, IC5.1
unnamed: CN$19.1, R$29.1
unnamed: C$38.1, C$39.1, CN$18.1, CN$19.2, D$34.1, L$9.1
unnamed: CN$21.2, D$37.1, D$38.2
unnamed: CN$21.3, D$39.2, D$40.1
unnamed: C6.-, D$37.2, D$40.2
unnamed: CN$21.1, D$36.2
unnamed: R$37.1, R$38.2
unnamed: D$42.2, R$38.1, R$39.2
unnamed: D$42.1, IC6.3
unnamed: CN$22.4, R$39.1, R$40.2
unnamed: C$43.2, R$40.1
unnamed: CN$22.3, R$41.2
unnamed: CN$23.3, L$12.2
unnamed: C6.+, L$12.1, R6.1
unnamed: C$42.2, CN$22.2
unnamed: C$41.2, C$42.1, D$41.2, R$36.2, R$37.2
unnamed: C$41.1, C$43.1, C$44.2, C$45.2, C$46.2, C$47.2, C$48.2, CN$24.4, R6.2, R$41.1
unnamed: C$48.1, CN$24.2, IC6.2, IC6.6
unnamed: C$45.1, D$38.1, D$39.1, L$11.2
unnamed: C$44.1, CN$22.5, D$36.1, IC6.4, IC6.8, R$42.1
unnamed: CN$24.1, IC6.7, R$42.2
unnamed: CN$24.3, IC6.1
unnamed: CN$23.1, R$36.1
unnamed: C$46.1, C$47.1, CN$22.1, CN$23.2, D$41.1, L$11.1
